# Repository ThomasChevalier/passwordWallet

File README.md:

# Password Wallet

Password Wallet is a physical password manager, working on every platforms by emulating an HID keyboard to interface with the computer.

## Description

Password Wallet is a USB device that can store credentials (passwords and user names) securely. The manipulation of the stored data as well as the various actions of restitution are available directly on the device which makes it an autonomous object, in the sense that a software is not necessary to use it. The device is designed to be reliable and robust, taking into account the sensitivity of the stored information. This project is what we could call a hardware password manager.
This object differs from software password managers by its portability: it is available on any operating system without prior installation, which facilitates implementation on computers with restricted access. Whereas most password managers offer to save data online to facilitate its transmission, and therefore expose this data to hackers, Password Wallet only stores data in its internal memory, so the identifiers are only gathered in one place, which ensures their security. In addition, its small size, approximately the size of a credit card, allows it to be stored in a pocket or bag.

## Features

* Credentials are AES-128 encrypted
* Unlock it with your RFID card
* Backup mechanism available if your card is lost
* Hardware random number generator based on clock jitter
* Store more than 800 credentials on the same device
* Sort credentials by their name, by date or by number of use
* Add, edit and delete credentials directly with the device
* Generate strong random passwords
* Highly durable memory, using Ferroelectric RAM
* High-contrast display using OLED technology
* Low power usage, maximizing notebook batteries
* Supports Qwerty and Azerty keyboards
* User-proof system, resists to unexpected disconnections
* Desktop application available to communicate with Password Wallet for easier managment

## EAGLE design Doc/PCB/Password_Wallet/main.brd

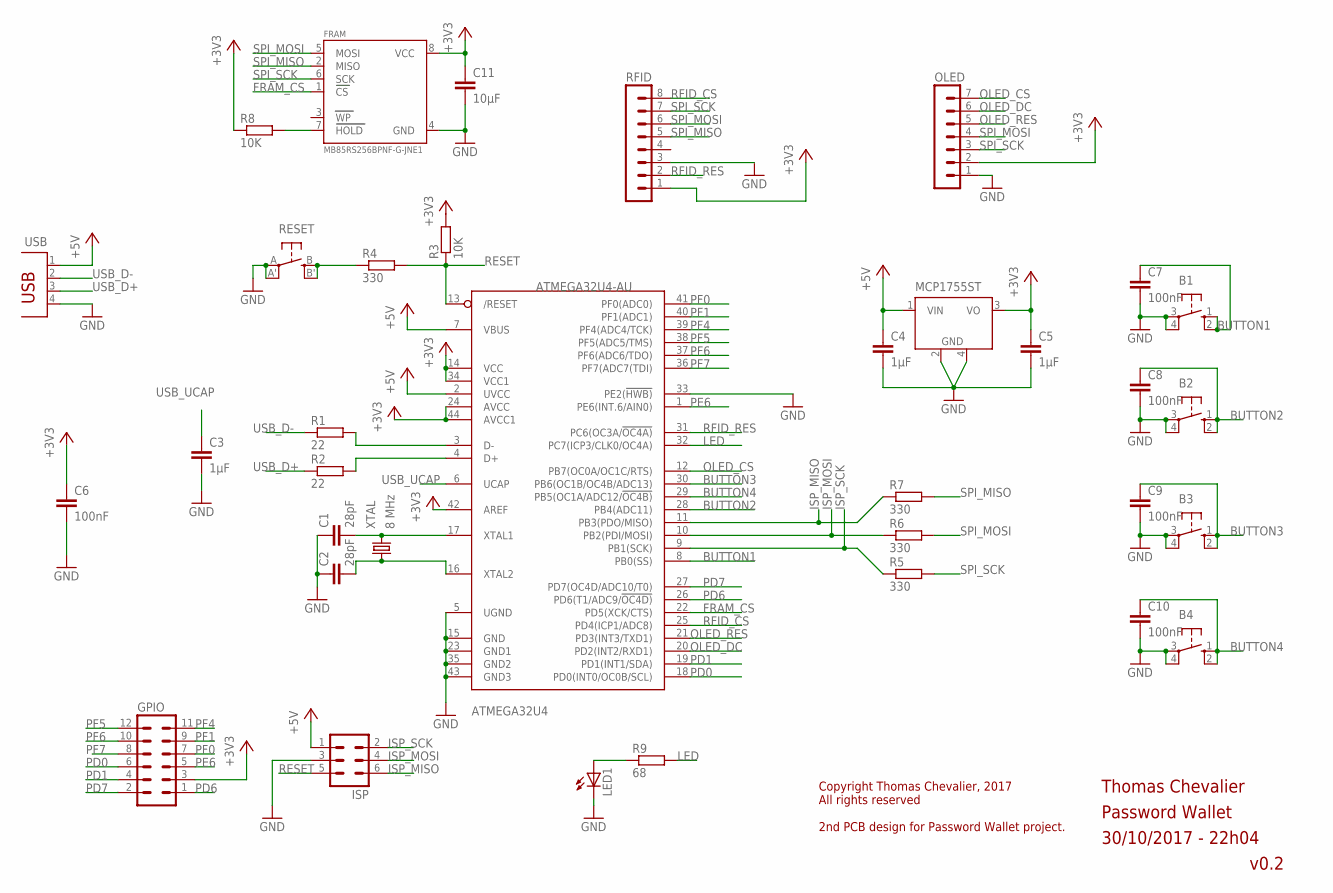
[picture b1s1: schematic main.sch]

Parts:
ATMEGA32U4: ATMEGA32U4-AU; TQFP44
B1, B2, B3, B4: 10-XX; B3F-10XX
C1, C2: 28pF; C0805
C3, C4, C5: 1µF; C0805
C6, C7, C8, C9, C10: 100nF; C0805
C11: 10µF; C0805
FRAM: MB85RS256BPNF-G-JNE1; SOIC8_150MIL
GPIO: MA06-2
ISP: MA03-2
LED1: LEDCHIP-LED0805; CHIP-LED0805
MCP1755ST: LM2936MP-3.0; SOT223
OLED: MA07-1
R1, R2: 22; R0805
R3, R8: 10K; R0805
R4, R5, R6, R7: 330; R0805
R9: 68; R0805
RESET: SPST_TACT-EVQQ2; EVQ-Q2
RFID: MA08-1
USB: PN87520
XTAL: 8 MHz; 5.0X3.2_2

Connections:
+3V3: ATMEGA32U4.14 (VCC), ATMEGA32U4.24 (AVCC), ATMEGA32U4.34 (VCC1), ATMEGA32U4.42 (AREF), ATMEGA32U4.44 (AVCC1), C5.1, C6.1, C11.1, FRAM.8 (VCC), GPIO.3, MCP1755ST.3 (VO), OLED.2, R3.2, R8.1, RFID.1
+5V: ATMEGA32U4.2 (UVCC), ATMEGA32U4.7 (VBUS), C4.1, ISP.1, MCP1755ST.1 (VIN), USB.1
BUTTON1: ATMEGA32U4.8 (PB0(SS)), B1.1 (S), B1.2 (S1), C7.1
BUTTON2: ATMEGA32U4.28 (PB4(ADC11)), B2.1 (S), B2.2 (S1), C8.1
BUTTON3: ATMEGA32U4.30 (PB6(OC1B/OC4B/ADC13)), B3.1 (S), B3.2 (S1), C9.1
BUTTON4: ATMEGA32U4.29 (PB5(OC1A/ADC12/!OC4B)), B4.1 (S), B4.2 (S1), C10.1
FRAM_CS: ATMEGA32U4.22 (PD5(XCK/CTS)), FRAM.1 (CS)
GND: ATMEGA32U4.5 (UGND), ATMEGA32U4.15 (GND), ATMEGA32U4.23 (GND1), ATMEGA32U4.33 (PE2(!HWB)), ATMEGA32U4.35 (GND2), ATMEGA32U4.43 (GND3), B1.3, B1.4 (P1), B2.3, B2.4 (P1), B3.3, B3.4 (P1), B4.3, B4.4 (P1), C1.1, C2.1, C3.2, C4.2, C5.2, C6.2, C7.2, C8.2, C9.2, C10.2, C11.2, FRAM.4 (GND), ISP.3, LED1.C, MCP1755ST.2 (GND), MCP1755ST.4 (GND), OLED.1, RESET.A, RESET.A' (P1), RFID.3, USB.4
ISP_MISO: ATMEGA32U4.11 (PB3(PDO/MISO)), ISP.6, R7.1
ISP_MOSI: ATMEGA32U4.10 (PB2(PDI/MOSI)), ISP.4, R6.1
ISP_SCK: ATMEGA32U4.9 (PB1(SCK)), ISP.2, R5.1
LED: ATMEGA32U4.32 (PC7(ICP3/CLK0/OC4A)), R9.2
unnamed: ATMEGA32U4.3 (D-), R1.2
unnamed: ATMEGA32U4.17 (XTAL1), C1.2, XTAL.2
unnamed: ATMEGA32U4.4 (D+), R2.2
unnamed: ATMEGA32U4.16 (XTAL2), C2.2, XTAL.1
unnamed: LED1.A, R9.1
unnamed: R4.1, RESET.B (S), RESET.B' (S1)
unnamed: FRAM.7 (HOLD), R8.2
OLED_CS: ATMEGA32U4.12 (PB7(OC0A/OC1C/RTS)), OLED.7
OLED_DC: ATMEGA32U4.20 (PD2(INT2/RXD1)), OLED.6
OLED_RES: ATMEGA32U4.21 (PD3(INT3/TXD1)), OLED.5
PD0: ATMEGA32U4.18 (PD0(INT0/OC0B/SCL)), GPIO.6
PD1: ATMEGA32U4.19 (PD1(INT1/SDA)), GPIO.4
PD6: ATMEGA32U4.26 (PD6(T1/ADC9/!OC4D)), GPIO.1
PD7: ATMEGA32U4.27 (PD7(OC4D/ADC10/T0)), GPIO.2
PE6: ATMEGA32U4.1 (PE6(INT.6/AIN0)), GPIO.5
PF0: ATMEGA32U4.41 (PF0(ADC0)), GPIO.7
PF1: ATMEGA32U4.40 (PF1(ADC1)), GPIO.9
PF4: ATMEGA32U4.39 (PF4(ADC4/TCK)), GPIO.11
PF5: ATMEGA32U4.38 (PF5(ADC5/TMS)), GPIO.12
PF6: ATMEGA32U4.37 (PF6(ADC6/TDO)), GPIO.10
PF7: ATMEGA32U4.36 (PF7(ADC7(TDI)), GPIO.8
RESET: ATMEGA32U4.13 (/RESET), ISP.5, R3.1, R4.2
RFID_CS: ATMEGA32U4.25 (PD4(ICP1/ADC8)), RFID.8
RFID_RES: ATMEGA32U4.31 (PC6(OC3A/!OC4A)), RFID.2
SPI_MISO: FRAM.2 (MISO), R7.2, RFID.5
SPI_MOSI: FRAM.5 (MOSI), OLED.4, R6.2, RFID.6
SPI_SCK: FRAM.6 (SCK), OLED.3, R5.2, RFID.7
USB_D+: R2.1, USB.3
USB_D-: R1.1, USB.2
USB_UCAP: ATMEGA32U4.6 (UCAP), C3.1

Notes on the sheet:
Password Wallet
30/10/2017 - 22h04
v0.2
Thomas Chevalier
Copyright Thomas Chevalier, 2017 All rights reserved 2nd PCB design for Password Wallet project.

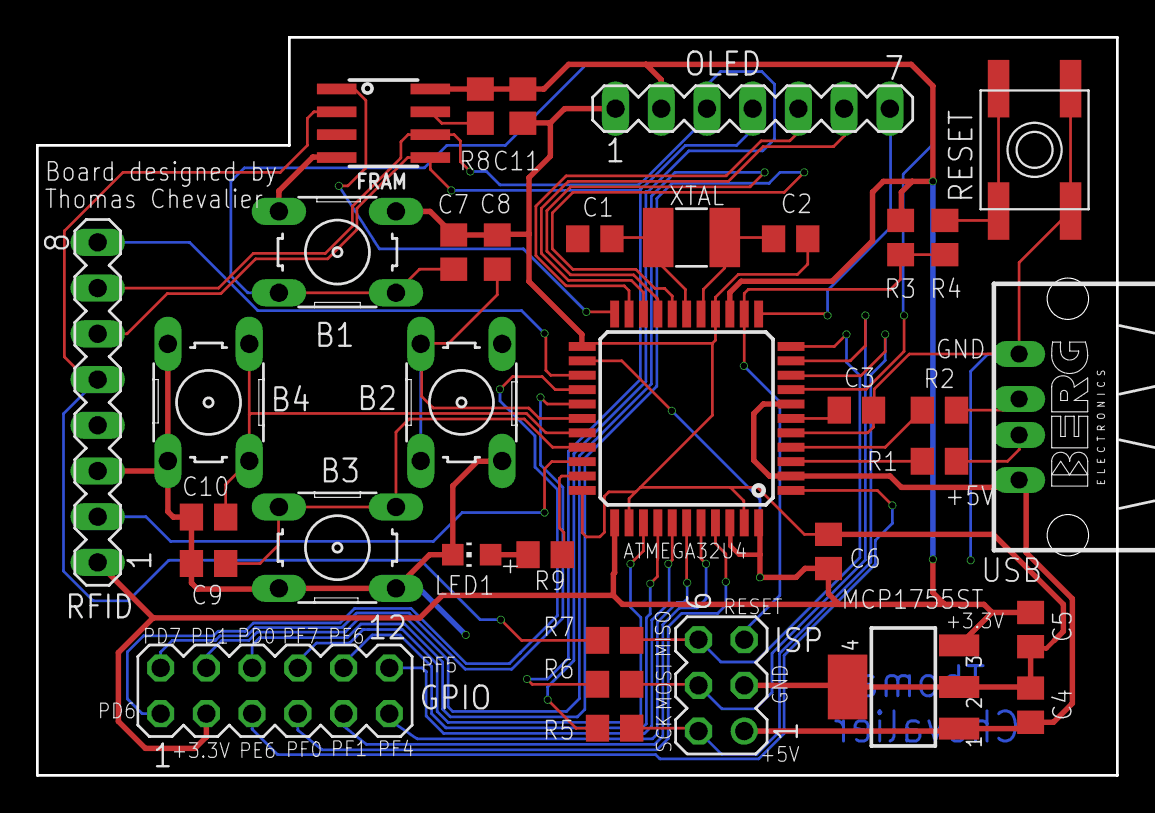
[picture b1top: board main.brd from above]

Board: 2 copper layers, 60.0 x 41.0 mm, 35 parts (0 on the bottom side), 42 nets.

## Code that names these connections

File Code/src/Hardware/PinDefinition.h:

/*
 * File generated by pindef_parser.
 * Copyright - Thomas Chevalier - 2017.
 * thomasom.chevalier@gmail.com
 * File created on 01-10-2019 16-35-01
*/

#ifndef PINDEFINITION_HEADER_THOMAS_CHEVALIER
#define PINDEFINITION_HEADER_THOMAS_CHEVALIER

//BUTTON
#define BUTTON_1_PIN_NUM 0
#define BUTTON_1_DDR DDRB
#define BUTTON_1_PORT PORTB
#define BUTTON_1_PIN PINB
#define BUTTON_1_PIN_CHANGE_NUM PCINT0

#define BUTTON_2_PIN_NUM 4
#define BUTTON_2_DDR DDRB
#define BUTTON_2_PORT PORTB
#define BUTTON_2_PIN PINB
#define BUTTON_2_PIN_CHANGE_NUM PCINT4

#define BUTTON_3_PIN_NUM 6
#define BUTTON_3_DDR DDRB
#define BUTTON_3_PORT PORTB
#define BUTTON_3_PIN PINB
#define BUTTON_3_PIN_CHANGE_NUM PCINT6

#define BUTTON_4_PIN_NUM 5
#define BUTTON_4_DDR DDRB
#define BUTTON_4_PORT PORTB
#define BUTTON_4_PIN PINB
#define BUTTON_4_PIN_CHANGE_NUM PCINT5


//FRAM
#define FRAM_CS_PIN_NUM 5
#define FRAM_CS_DDR DDRD
#define FRAM_CS_PORT PORTD
#define FRAM_CS_PIN PIND


//LED
#define LED_PIN_NUM 7
#define LED_DDR DDRC
#define LED_PORT PORTC
#define LED_PIN PINC


//OLED
#define OLED_CS_PIN_NUM 7
#define OLED_CS_DDR DDRB
#define OLED_CS_PORT PORTB
#define OLED_CS_PIN PINB

#define OLED_DC_PIN_NUM 2
#define OLED_DC_DDR DDRD
#define OLED_DC_PORT PORTD
#define OLED_DC_PIN PIND

#define OLED_RES_PIN_NUM 3
#define OLED_RES_DDR DDRD
#define OLED_RES_PORT PORTD
#define OLED_RES_PIN PIND


//RFID
#define RFID_CS_PIN_NUM 4
#define RFID_CS_DDR DDRD
#define RFID_CS_PORT PORTD
#define RFID_CS_PIN PIND

#define RFID_RES_PIN_NUM 6
#define RFID_RES_DDR DDRC
#define RFID_RES_PORT PORTC
#define RFID_RES_PIN PINC


//SPI
#define SPI_SS_PIN_NUM 0
#define SPI_SS_DDR DDRB
#define SPI_SS_PORT PORTB
#define SPI_SS_PIN PINB

#define SPI_SCK_PIN_NUM 1
#define SPI_SCK_DDR DDRB
#define SPI_SCK_PORT PORTB
#define SPI_SCK_PIN PINB

#define SPI_MOSI_PIN_NUM 2
#define SPI_MOSI_DDR DDRB
#define SPI_MOSI_PORT PORTB
#define SPI_MOSI_PIN PINB

#define SPI_MISO_PIN_NUM 3
#define SPI_MISO_DDR DDRB
#define SPI_MISO_PORT PORTB
#define SPI_MISO_PIN PINB


// INIT VALUE
#define DDRB_INIT_VALUE ((1 << OLED_CS_PIN_NUM) | (1 << SPI_SS_PIN_NUM) | (1 << SPI_SCK_PIN_NUM) | (1 << SPI_MOSI_PIN_NUM) | 0)
#define PORTB_INIT_VALUE ((1 << BUTTON_1_PIN_NUM) | (1 << BUTTON_2_PIN_NUM) | (1 << BUTTON_3_PIN_NUM) | (1 << BUTTON_4_PIN_NUM) | (1 << OLED_CS_PIN_NUM) | 0)

#define DDRC_INIT_VALUE ((1 << LED_PIN_NUM) | (1 << RFID_RES_PIN_NUM) | 0)
#define PORTC_INIT_VALUE ((1 << RFID_RES_PIN_NUM) | 0)

#define DDRD_INIT_VALUE ((1 << FRAM_CS_PIN_NUM) | (1 << OLED_DC_PIN_NUM) | (1 << OLED_RES_PIN_NUM) | (1 << RFID_CS_PIN_NUM) | 0)
#define PORTD_INIT_VALUE ((1 << FRAM_CS_PIN_NUM) | (1 << RFID_CS_PIN_NUM) | 0)

#define INIT_ALL_DDR DDRB = DDRB_INIT_VALUE; \
DDRC = DDRC_INIT_VALUE; \
DDRD = DDRD_INIT_VALUE; \

#define INIT_ALL_PORT PORTB = PORTB_INIT_VALUE; \
PORTC = PORTC_INIT_VALUE; \
PORTD = PORTD_INIT_VALUE; \


#endif // PINDEFINITION_HEADER_THOMAS_CHEVALIER

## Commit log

2016-10-20 Cleaning
2016-10-20 Option menu done
2016-10-20 Work on passwords functions
2016-10-20 Work on transisitions Option Browse and Main
2016-10-20 Add pin definition file
2016-10-21 Add 4th button, update some code
2016-10-21 Spi freeze bug corriged ! Browse menu working
2016-10-22 Get rfid working
2016-10-22 Clean rfid code
2016-10-22 The menus work !
2016-10-22 Change in menus
2016-10-22 Rotation 180
2016-10-23 Add rotation to the options
2016-10-23 Add typing screen
2016-10-23 Random number generation, work on change master key
2016-10-24 Fix entropy pool overflow
2016-10-24 Add random generation of printable character
2016-10-27 Fix issue in request_printable
2016-10-27 Add encryption and decryption function for entropy pool
2016-10-27 Add organisation files
2016-10-27 Remove entropy pool encryption because it cannot be authenticated.
2016-10-27 Reduce program size and data size by using -flto option !
2016-10-27 New string method and add -Os to linker, reducing code size
2016-10-27 Add fram integration choice
2016-12-20 Add a little documentation and work on pwd functions
2016-12-20 Change padding method, add globals definition, add add_pwd function
2016-12-20 Fix typing screen issue
2016-12-22 Add partial handling of the memory map
2016-12-22 Fix password and username storage
2016-12-22 Work on change_master_key
2016-12-26 Add messages
2016-12-26 Correction
2016-12-27 New makefile
2016-12-30 Bug fix in fram read id
2016-12-30 Add constant for spi pin id
2016-12-30 Change cpu frequency from 16MHz to 8MHz
2017-01-22 Work on progress bar and recovery options
2017-01-28 Change random generation
2017-02-15 Small updates and fix, add Lufa directory
2017-02-15 Clean lufa dir
2017-02-17 Full integration of LUFA library, device can now work as a keyboard. Refactorisation
2017-02-18 Refactoring code and folders, clear LUFA directory
2017-02-18 Change states creation, and refactor code
2017-02-19 Add states, reindent, upgrade code
2017-02-19 Clean code (password & co)
2017-02-20 Add font, add better password list management
2017-02-22 Fix password navigation
2017-02-23 Work on sorting algoritms (not working yet), add useful folder to repository
2017-02-25 Change directory organisation, add Led files, upload a bootloader on the atmega32u4 (no need to use isp programming anymore), code optimizations, and more ...
2017-02-25 Remove qt build files'
2017-02-26 Add virtual serial port to talk with pc
2017-02-26 Full serial communication
2017-02-26 Update code, fix serial implementation
2017-02-27 Add an utility and replace codeblocks project by makefile. Fix serial communication
2017-03-01 Minor fix
2017-03-01 Fix keyboard
2017-03-05 Remove MEMORY_MAP global variable
2017-03-05 Reduce size of the get_prev_id_sort_none function
2017-03-06 Fix TotalInterfaces count in descriptor implementation
2017-03-06 Fix the association between virtualSerial and keyboard
2017-03-06 Little clean up and add warning message on change master key
2017-03-06 Add EEPROM constant for offset
2017-03-10 Improve speed of transmission when pc send data to the device
2017-03-12 Reduce code size
2017-03-14 Fix keycode
2017-03-18 Add qwerty option, reduce code size, try to get a stable code by setting the clock to 8Mhz
2017-04-10 Add message for reset source, add calls to sorting method
2017-04-30 Add azerty keyboard layout
2017-05-07 [WIP] Add documentation
2017-06-09 Add documentation and reduce code size
2017-07-12 Add I2C fram support. Fix list sorting. Random improvement.
2017-07-12 Fix ascii 85 encoding
2017-07-12 Work on desktop app. Minor changes (typo)
2017-07-15 Syntax fix and refactor desktop app + resolving function
2017-07-20 Fix font problem. Add pcb dir. Work on desktop app.
2017-07-20 Speed up compilation. Reduce code size
2017-07-20 Remove debug information
2017-07-21 Reduce oled_init code size
2017-07-21 Move internal function of oled in implementation file
2017-07-21 Fix random char generation ('~' is now generated), reduce code size
2017-07-21 Add serial to file tool
2017-07-21 Fix self test bug where rfid was not initialized
2017-07-21 Indentation
2017-08-06 Reduce aes code size
2017-08-06 Add web site of the aes code
2017-08-06 Fix #7
2017-08-07 [WIP] Refactor options selection. Does not work very well yet.
2017-08-08 Refactor option system. Fix #8
2017-08-08 Add gpio to reduce code size. Fix #15
2017-08-08 Group spi setup in one function. Fix #9
2017-08-08 Fix browse dock blinking
2017-08-08 Fix #27, add a bit of doc
2017-08-08 Replace State_Recovery by a list of option
2017-08-08 Remove no encryption option. Fix #24
2017-08-09 Add sleep mode. Fix #12
2017-08-09 Improve keyboard. Todo : add '<' and '>' key. Use caps lock
2017-08-10 Modify self test delays
2017-08-10 Fix wrong attribute in descriptior (self powered)
2017-08-11 Minor change. Add minimal example to the led problem
2017-08-11 Add a new utility to manage the pin attribution. Fix #19. Add doc
2017-08-12 Disable sleep when connected to the app
2017-08-12 Refactor string storage : add a small program to handle that.
2017-08-12 Remove String.c
2017-08-12 Declare oled data extern to fix #21. Remove '~' (tilde) from the accepted input. On windows the tilde is inserted by pressing two times the key whereas on linux it is inserted when typed one time the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
2017-08-12 Remove -s option to execute make symbol-sizes command
2017-08-12 Update the gui to the new memory model (no entropy pool size). Fix a endian bug.
2017-08-12 Redesign main interface
2017-08-12 Add more space between words, change draw_text function so no strlen is needed (more robust)
2017-08-12 Add browse by name functionnality
2017-08-12 Change sort by use order
2017-08-13 Add a backup system. If a reset occurs during the update of a pwd or a usr name the password will be restored to the value before the update; If a reset occurs during the update of the master key the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
2017-08-14 Add security in backup system and add an option to force the use of a key
2017-08-14 Stop the encryption process if there is a zero. Rename a file and change pos of text
2017-08-14 Add center x option for str. Remove small font. Fix type strings artefacts.
2017-08-14 Fix underflow issue in string_parser
2017-08-14 Update drawing func to align the text.
2017-08-14 Add system info view
2017-08-15 Improve a bit system info. Refactor functions name
2017-08-16 Add a menu to send password
2017-08-17 Add counter display
2017-08-17 Little fix. Add a note that describe how to install a bootloader. Install a dfu bootloader
2017-08-28 Many changes. Improve code for device, work on gui and on the memory parser. Add lib dir
2017-08-28 Begin the refactorisation of the Serial interface of the gui
2017-09-06 [WIP] Change SerialDevice implentation in the IHM
2017-09-24 Redesign the communication protocol in a more robust way. Not tested yet
2017-09-24 Remove old file
2017-09-29 Add timeout timer for the serial com. Remove state_communication.
2017-09-29 Add new line on the end of file
2017-09-30 Remove kicad files
2017-09-30 Fix bugs in serial communication
2017-09-30 Little bug fix in serial communication
2017-10-13 Communication is fully functionnal. Add a logo when data are exchanged. Create a serial console
2017-10-15 Fix #25 : store some constants in eeprom.
2017-10-15 Remove key erasing
2017-10-23 Little (unsuccessful) test to save option list in flash
2017-10-23 When the screen is reversed, all work well
2017-10-23 Add vcc graph
2017-10-24 Add version info
2017-10-24 Add key entered event and fix a bug in the desktop app wich lead to an invalid command transmission
2017-10-30 Minor change in embedded code. Work on the interface
2017-10-30 Update notes
2017-10-30 Changes in note to make them more printable
2017-10-31 The screen reverse operation is now simpler
2017-11-19 Fix a bug in the rng. Include some utilities in makefile. Add a description text file
2017-11-19 Clean folders. Add sample of random data generated by the device
2017-11-29 Add support for 16 bit password address
2017-11-29 Add doc
2017-12-11 Work on interface and reindent some files
2017-12-28 Doc and minor change
2017-12-29 Put the µc in idle mode when waiting. Reduce a bit the code size (lufa defines)
2017-12-29 Minor changes on commands.
2018-01-03 Add confirmation screen
2018-01-03 Minor improvements
2018-01-06 Add a dialog to resolve problems in the interface
2018-01-06 Remove 'force card' option from recovery mode
2018-01-06 Optimize buttons_pressed
    modifié : src/Hardware/Buttons.c
2018-01-06 Reduce code size by creating a function for _delay_ms
2018-02-15 Doc and minor changes
2018-02-28 Add travis
2018-02-28 Correct travis file
2018-02-28 General build system
2018-02-28 Update travis
2018-02-28 Update Readme with travis result
2018-03-01 Add a note on fuses
2018-03-01 Removed unnecessary files from the repo
2018-03-05 Update pins to match the pcb
2018-03-05 Update files to work with the pcb
2018-03-06 Add a debouncing algorithm
2018-03-06 Make the program compatible with the full fram memory (1Mbit)
2018-03-06 Remove loop that force to release buttons and forbid access to pwd menu if no pwd
2018-03-07 Fix a bug in the rfid driver
2018-03-07 Fix a bug in the handling of pwd id. Improve power management
2018-03-07 Add a memory editor
2018-03-07 .gitignore
2018-03-09 Increase message size in the serial protocol and improve the mem editor
2018-03-09 Add a program to transfer fram content from the pc to the device
2018-03-09 Improve random generator of memory editor
2018-03-09 Add bootloader to the repo. Add a reset command
2018-04-17 Implement a more secure method to compare two blocks of memory
2018-06-03 Add a configuration file for the list of options. The list is now stored in flash (90 bytes saved only...)
2018-06-03 Fix wrong file name
2018-08-16 Migration
2018-11-16 Create LICENSE
2018-12-01 Fix a bug in the backup system that can lead to data loss
2019-09-13 Minor changes
2019-09-13 Add pictures of PCB
2019-09-18 Fix makefile of string_parser
2019-09-18 Travis
2019-09-18 Typo
2019-10-01 Comment and format
2019-12-04 Add 'sudo' to write with the bootloader on the device
2019-12-05 Try to put the device into sleep while communicating with a tag
2020-04-19 Enhance readme and add a gif overview

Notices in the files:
parts and their libraries:
microbuilder: This work is placed in the public domain, and may be freely used for commercial and non-commercial work with the following conditions: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
crystal-geyer_V1_0: Copyright: Geyer-Electronic
